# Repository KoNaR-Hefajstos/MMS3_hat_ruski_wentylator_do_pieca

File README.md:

# Hat ruski wentylator do pieca

## Sekcja 1: Dokumentacja Hat'a

### Krótki opis projektu
Dedykowany moduł sterujący przeznaczony do obsługi ruskiego wentylatora pieca . Urządzenie bazuje na mikrokontrolerze **CH32V003**, który realizuje zadania regulacji napięcia zasilania silnika, sterowania kluczem PWM, pomiaru prędkości obrotowej z czujnika Halla i reguluje prędkość obrotową przy użyciu regulatora PID.

Moduł wyposażono w przetwornicę podwyższającą (Boost) sterowaną cyfrowym potencjometrem MCP4161 oraz stopień wykonawczy typu **high-side switch** oparty na tranzystorze PMOS.

Komunikacja po I2C

### Zgodność ze standardem ChainBus

* ✅  Używa złącza ChainBus, nie zmienia jego miejsca ani pinoutu.
* ✅  Używa wyłącznie interfejsów I2C, SPI lub UART i nie inicjuje samodzielnie nowych transmisji (Nie jest master'em I2C albo SPI).
* ✅  Spełnia wymagania mechaniczne standardu (wymiary PCB, rozstaw otworów).
* ✅  Pobiera maksymalny prąd zgodny z ilością na jednego hat'a
* ❌ Obsługuje napięcie wejściowe BRD_VIN do wartości 48V. ---> napięcie wejściowe max 40V. Zawsze podaje napięcie wejściowe na wyjście wentylatora (J6 pin 3)

### Komunikacja i adresowanie

#### Adresacja I2C
Komunikacja z płytą główną ChainBus odbywa się za pośrednictwem magistrali I2C podłączonej do mikrokontrolera CH32V003.

| Układ (IC)   | Funkcja                              |     Adres I2C (7-bit)     |
| :----------- | :----------------------------------- | :-----------------------: |
| **CH32V003** | Mikrokontroler (zarządzanie modułem) | *Konfigurowalny w sofcie* |

### Pinout mikrokontrolera CH32V003

| Pin MCU | Nazwa sygnału | Kierunek | Opis funkcjonalny                                  |
| :------ | :------------ | :------: | :------------------------------------------------- |
| **PC0** | `PWM_GATE`    | Wyjście  | Sterowanie bramką PMOS (high-side switch)          |
| **PC1** | `SDA`         | Wej/Wyj  | Linia danych magistrali I2C (ChainBus)             |
| **PC2** | `SCL`         | Wejście  | Linia zegarowa magistrali I2C (ChainBus)           |
| **PC3** | `BOOST_EN`    | Wyjście  | Włączenie przetwornicy Boost (`1` = ON, `0` = OFF) |
| **PC4** | `V_MONITOR`   | Wejście  | Pomiar ADC napięcia silnika (dzielnik 36k / 2k)    |
| **PC5** | `SPI_SCK`     | Wyjście  | Zegar SPI do potencjometru MCP4161                 |
| **PC6** | `SPI_MOSI`    | Wyjście  | Dane wyjściowe SPI do potencjometru MCP4161        |
| **PC7** | `SPI_MISO`    | Wejście  | Dane wejściowe SPI z potencjometru MCP4161         |
| **PD0** | `HALL_INPUT`  | Wejście  | Sygnał z czujnika Halla wentylatora                |
| **PD2** | `SPI_CS_POT`  | Wyjście  | Wybór układu (Chip Select) dla MCP4161             |
| **PD3** | `GPIO_PD3`    | Wej/Wyj  | Wolny pin GPIO wyprowadzony na złącze J9           |
| **PD4** | `GPIO_PD4`    | Wej/Wyj  | Wolny pin GPIO wyprowadzony na złącze J9           |
| **PD5** | `USART_TX`    | Wyjście  | Port szeregowy TX (debugowanie, złącze J9)         |
| **PD6** | `USART_RX`    | Wejście  | Port szeregowy RX (złącze J9)                      |

---

### Pinout złączy zewnętrznych

#### J6 — Złącze wentylatora pieca
Złącze przeznaczone do bezpośredniego podłączenia ruskiego wentylatora.

| Pin złącza | Kolor przewodu z wentlatora | Nazwa sygnału | Opis                                                |
| :--------: | :-------------------------- | :------------ | :-------------------------------------------------- |
|   **1**    | Czarny                      | `GND`         | Wspólna masa układu                                 |
|   **2**    | Brązowy                     | `5V`          | Zasilanie układu Halla wentylatora                  |
|   **3**    | Niebieski                   | `VCC_MOTOR`   | Napięcie zasilające silnik wentylatora              |
|   **4**    | Biały/Żółty                 | `HALL`        | Wyjście czujnika Halla (sprzężenie zwrotne obrotów) |

#### J9 — Złącze wolnych pinów mcu

| Pin złącza | Sygnał | Opis                    |
| :--------: | :----- | :---------------------- |
|   **1**    | `GND`  | Masa układu             |
|   **2**    | `3V3`  | Zasilanie logiki 3.3V   |
|   **3**    | `PD3`  | Wolny port GPIO         |
|   **4**    | `PD4`  | Wolny port GPIO         |
|   **5**    | `PD5`  | GPIO + Wyjście USART TX |
|   **6**    | `PD6`  | GPIO + Wejście USART RX |

---

### Konfiguracja i zasada działania stopni wykonawczych

#### 1. Regulacja Napięcia (Przetwornica Boost)
Napięcie zasilania silnika jest generowane przez przetwornicę podwyższającą z poziomu wejściowego 12V. Napięcie wyjściowe regulowane jest przy użyciu potencjometru cyfrowego MCP4161 (5kΩ) działającego jako rezystor nastawny w feedback'u regulatora . Wyjście `P0B` podłączone jest z jednej strony, natomiast wyjścia `P0W` i `P0A` są ze sobą zwarte z drugiej.

Napięcie wyjściowe definiuje zależność:
$$U_{out} = 1.25 \times \left(1 + \frac{50\text{k}\Omega}{1.22\text{k}\Omega + R_{trim}}\right)$$

*   **⚠️ KRYTYCZNE OGRANICZENIE BEZPIECZEŃSTWA:** Mimo teoretycznego zakresu regulacji przetwornicy od 12V do 60V, **maksymalne dopuszczalne napięcie robocze wynosi 24V**. Przekroczenie tego progu spowoduje nieodwracalne uszkodzenie wentylatora, kondensatorów filtrujących oraz stopnia high-side switch. (24V silnika, a ~40V kondensatorów)
*   **Procedura bezpiecznego startu:** Przy każdym uruchomieniu mikrokontrolera, oprogramowanie musi natychmiast ustawić potencjometr MCP4161 na **maksymalną rezystancję (5kΩ)**, co wymusza minimalne napięcie startowe (ok. 11.3V). Dodatkowo, przetwornica Boost oraz klucz PWM muszą być domyślnie wyłączone (`BOOST_EN` = `0`, `PWM_GATE` = `0`).
*   **Charakterystyka Boost:** Nawet w stanie wyłączonym (`BOOST_EN` = `0`), napięcie wejściowe 12V będzie stale obecne na wyjściu przetwornicy.

#### 2. Bonusowy Stopień wykonawczy (High-Side Switch PMOS)
Sterowanie dopływem prądu z przetwornicy do silnika wentylatora odbywa się za pomocą klucza high-side switch opartego na tranzystorze PMOS.

*   **Konfiguracja domyślna (Bypass):** Na płycie fabrycznie wlutowany jest rezystor **R6**, który zwiera (pomija) tranzystor PMOS. W tym trybie silnik zasilany jest stale bezpośrednio z wyjścia przetwornicy Boost, a regulacja obrotów odbywa się wyłącznie poprzez zmianę jej napięcia wyjściowego.
*   **Konfiguracja zaawansowana (Sterowanie PWM):** W celu sterowania silnikiem za pomocą cięcia prądu sygnałem PWM z pinu `PC0` mikrokontrolera, należy **odlutować rezystor R6**.
*   **Element wykonawczy:** Na płycie domyślnie znajduje się tranzystor PMOS **AO3401A** (obudowa SOT-23, parametry: 30V, 4A), który jest w pełni wystarczający do obsługi docelowego wentylatora piecowego. Na laminacie pozostawiono jednak alternatywne, wolne miejsce na montaż mocniejszego tranzystora w obudowie **TO-220** na wypadek nietypowych modyfikacji.

#### A po ludzku
* Masz wentlator, sterujesz jego prękością dając mu różne napięcie i/lub PWM
* Napięciem sterujesz przez potencjometr cyfrowy
* PWM przez high side switch (który jest domyślnie z'bypass'owany czyli trzeba wylutować rezystor żeby go użyć)
* Przetworke możesz właczyć/wyłączyć, ale zawsze daje VIN na wyjście silnika
* Prędkość obrotową wentylatora możesz odczytać przez częstotliwosć impulsów na czujnika halla
* A napięcie wyjściowe przetworki jest po dzielniku napięć na pin'ie PC4 (dzielnik dzieli VCC silnika przez 18)

---

### Gotowe arkusze hierarchiczne
W projekcie zaprojektowano i użyto następujących arkuszy hierarchicznych:
* **CH32v003** – Schemat mikrokontrolera głównego wraz z elementami pasywnymi i złączem programowania
* **Boost converter** – Układ regulowanej przetwornicy podwyższającej napięcie z 12V na zakres do ~60V sterowanej cyfrowym potencjometrem MCP4161.
* **High side switch** – Blok High-side switch'a na PMOS (AO3401A) sterowanego sygnałem PWM z układem typu totem pole do drive'owania bramki
---

## Sekcja 2: Specyfikacja standardu ChainBus

### Architektura i łączenie modułów
Standard ChainBus umożliwia modułowe łączenie hatów. Na jednym MMS3 można zamontować pionowo **do 8 hat'ów**. Połączenie realizowane jest poprzez wpięcie złącza męskiego kolejnego hat'a w złącze żeńskie poprzedniego

### Komunikacja i sterowanie
Magistrala ChainBus jest w pełni cyfrowa. Płyta główna nie steruje bezpośrednio sygnałami ogólnego przeznaczenia (GPIO) na poszczególnych hat'ach. Wszelkie operacje (np. obsługa diod LED, odczyt krańcówek, generowanie sygnałów PWM) muszą być realizowane przez dedykowane układy scalone (np. ekspandery portów, sterowniki) komunikujące się przez interfejsy systemowe.

*Przykład:*
`MCU` $\rightarrow$ `Expander GPIO po I2C` $\rightarrow$ `Dioda LED`

Wybór aktywnego modułu realizowany jest przez układ przełącznika magistrali (bus switch) na płycie głównej. Dzięki temu linie I2C, SPI i UART są niezależne dla każdego hat'a (brak konfliktów adresów I2C między różnymi hatami).
* **Identyfikacja:** Każdy moduł powinien posiadać pamięć EEPROM na magistrali I2C w celu identyfikacji płyty przez system - układ M24C64-W skonfigurowany na adres `1010000` przy liniach adresowych A0, A1, A2 zwartych do masy.

### Zasilanie
Złącze ChainBus dostarcza następujące linie zasilania:

| Magistrala zasilania | Napięcie znamionowe | Maksymalny prąd (łączny dla 8 hatów) | Szacowany prąd na jeden hat |
| :------------------- | :-----------------: | :----------------------------------: | :-------------------------: |
| **5V**               |        5.0 V        |                1.0 A                 |           125 mA            |
| **12V stby**         |       12.0 V        |                0.5 A                 |            65 mA            |
| **BRD_VIN**          |   12.0 V – 48.0 V   |                1.5 A                 |           185 mA            |

*   Komponenty podłączone do linii `BRD_VIN` muszą być przystosowane do pracy z napięciem od 12V do **48 V**.
*   W przypadku zapotrzebowania na wyższą moc, dopuszczalne jest zastosowanie dodatkowego złącza zasilania XT60 (obciążalność do ok. 60 A).

### Wymagania mechaniczne i złącza
* **Wymiary PCB:** Niedozwolona jest zmiana obrysu płytki oraz położenia otworów montażowych, aby zachować kompatybilność mechaniczną.
* **Pozycjonowanie złączy ChainBus:** Położenie złącza standardu 2x16 SMD (raster 2.54 mm) musi być zgodne z szablonem. Złącze żeńskie montowane jest na stronie FRONT, natomiast złącze męskie na stronie BACK.
* **Interfejsy zewnętrzne:** Złącza wejścia/wyjścia (domyślnie standard JST-XH 2.5 mm o obciążalności do 3 A) oraz opcjonalne złącze XT60 powinny być umieszczone przy dolnej krawędzi płytki. Elementy regulacyjne i sygnalizacyjne (potencjometry, przełączniki, diody LED) należy lokalizować przy prawej krawędzi płytki.
* **Komponenty** Wszystkie komponenty powinny być na stronie front płytki żeby nie haczyły o elementy ze wcześniejszego hat'a

---

## Sekcja 3: Licencje

### Licencje projektu

*   **PCB:** CERN-OHL-P
*   **Software:** MIT License

[Template](https://github.com/KoNaR-Hefajstos/MMS3_hat_templates/) jest na licencji CC0 1.0 Universal. **Reszta projektu nie jest na tej licencji**

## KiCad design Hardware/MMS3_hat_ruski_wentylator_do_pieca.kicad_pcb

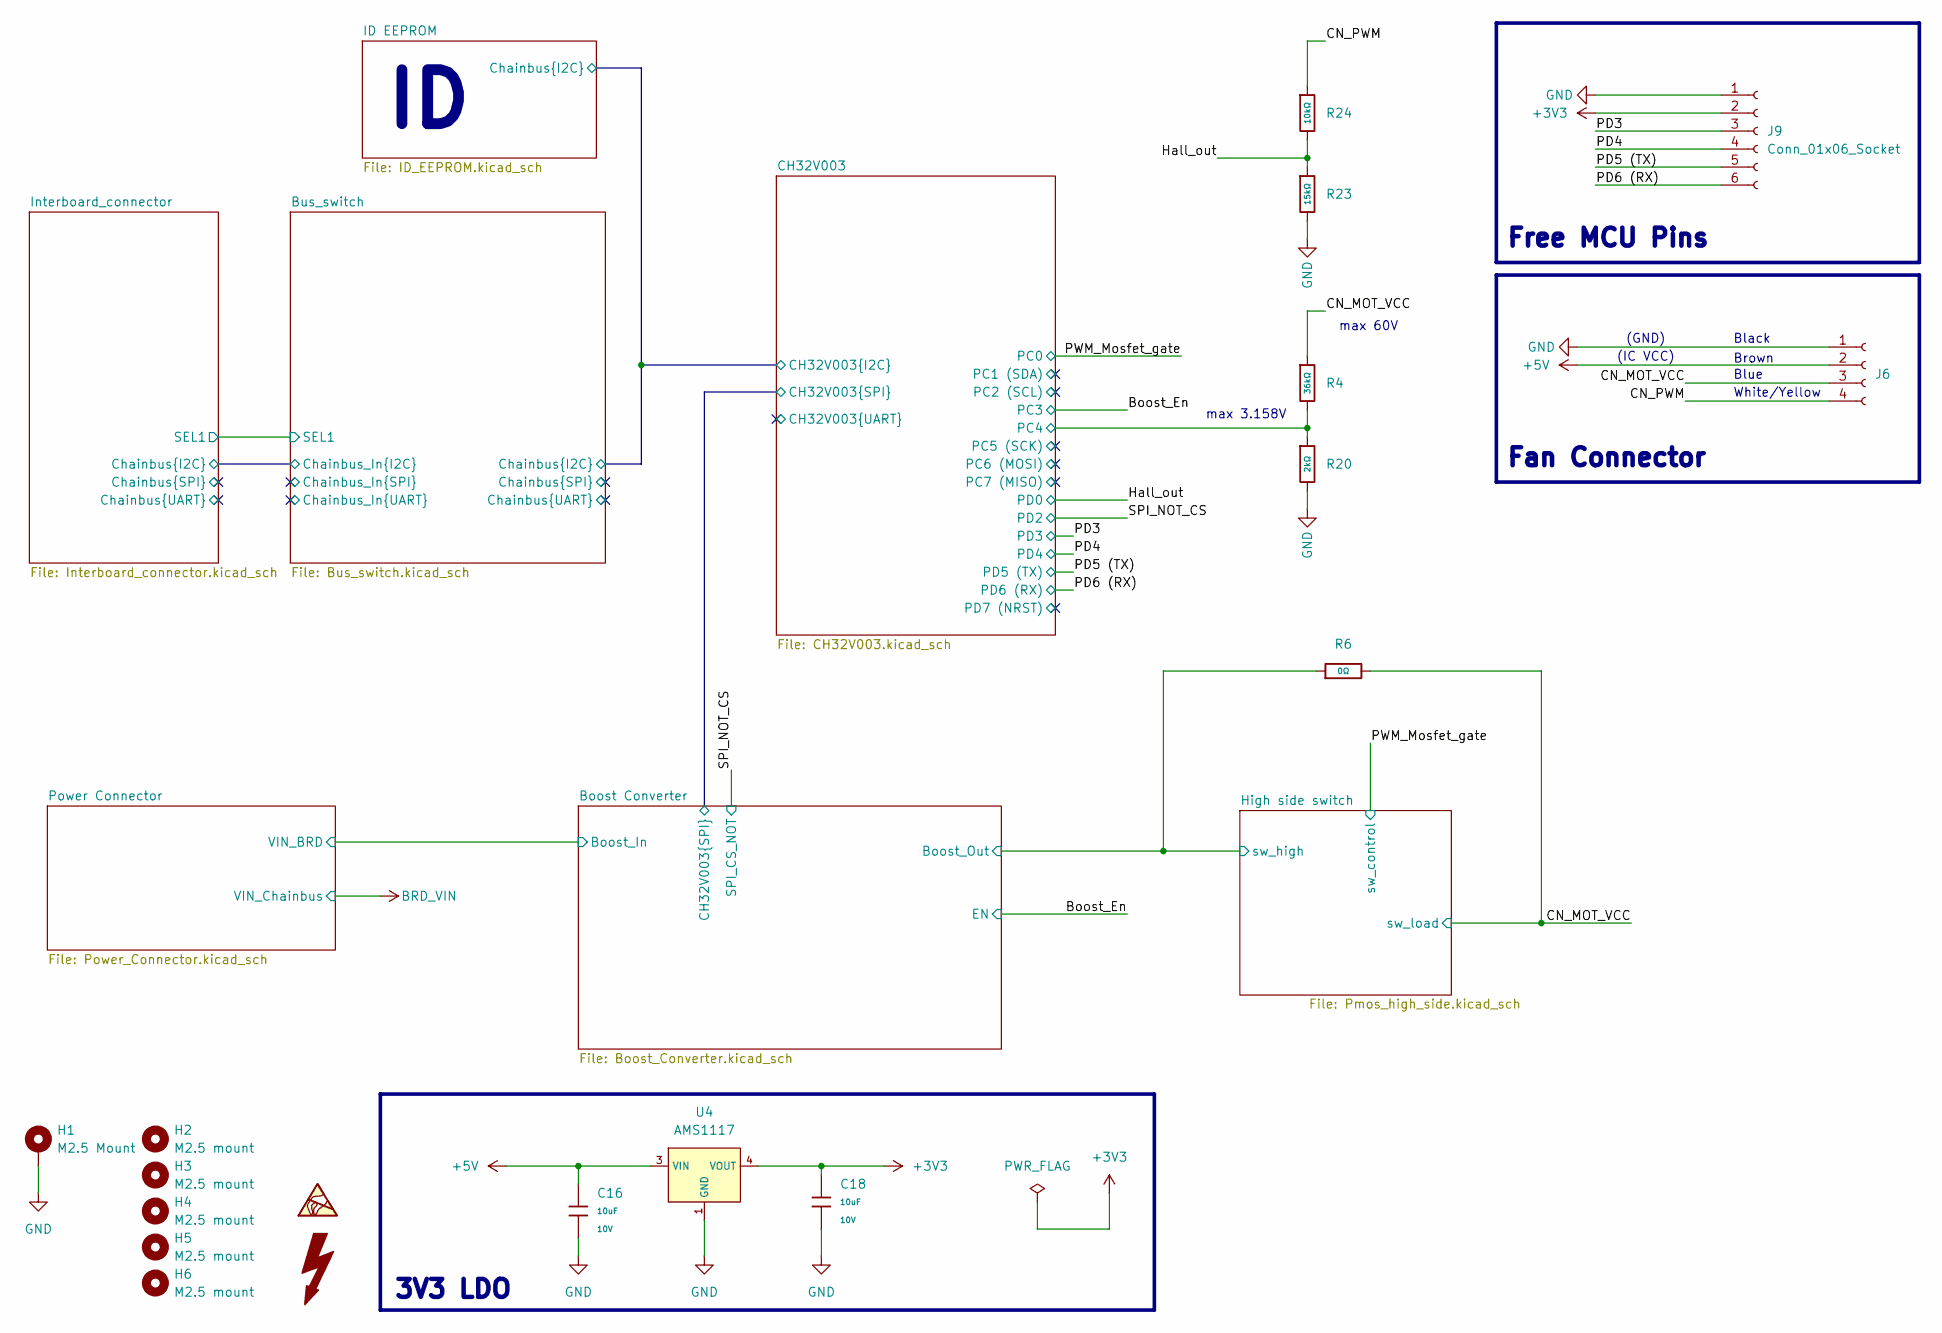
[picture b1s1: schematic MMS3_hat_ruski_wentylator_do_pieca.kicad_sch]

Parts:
C16, C18: 10uF; C_0603; Voltage Rated 10V; Tolerance ±10%; Part CL10A106KP8NNNC; LCSC C19702
H1: M2.5 Mount; MountingHole_2.7mm_M2.5_DIN965_Pad_TopOnly
H2, H3, H4, H5, H6: M2.5 mount; MountingHole_2.7mm_M2.5
J6: Conn_01x04_Socket; JST_XH_S4B-XH-A_1x04_P2.50mm_Horizontal
J9: Conn_01x06_Socket; JST_XH_S6B-XH-A_1x06_P2.50mm_Horizontal
R4: 36kΩ; R_0603; Overload Voltage (Max) 75V; Tolerance ±1%; Part 0603WAF3602T5E; LCSC C23147
R6: 0Ω; R_0603; Overload Voltage (Max) 75V; Tolerance ±1%; Part 0603WAF0000T5E; LCSC C21189
R20: 2kΩ; R_0603; Overload Voltage (Max) 75V; Tolerance ±1%; Part 0603WAF2001T5E; LCSC C22975
R23: 15kΩ; R_0402; Overload Voltage (Max) 50V; Tolerance ±1%; Part 0402WGF1502TCE; LCSC C25756
R24: 10kΩ; R_0402; Overload Voltage (Max) 50V; Tolerance ±1%; Part 0402WGF1002TCE; LCSC C25744
U4: AMS1117; SOT-223-3_L6.5-W3.4-P2.30-LS7.0-BR; Output Voltage 3.3V; Dropout Voltage 1.3V@(800mA); Part AMS1117-3.3; LCSC C6186

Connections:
+3V3: C18.1, J9.2, U4.2 (VOUT), U4.4 (VOUT); also elsewhere on the board
+5V: C16.1, J6.2, U4.3 (VIN); also elsewhere on the board
/Boost Converter/Boost_Out: R6.1; also elsewhere on the board
/CH32V003/PC4: R4.2, R20.1; also elsewhere on the board
/CN_MOT_VCC: J6.3, R4.1, R6.2; also elsewhere on the board
/CN_PWM: J6.4, R24.1
/Hall_out: R23.1, R24.2; also elsewhere on the board
/PD3: J9.3; also elsewhere on the board
/PD4: J9.4; also elsewhere on the board
/PD5 (TX): J9.5; also elsewhere on the board
/PD6 (RX): J9.6; also elsewhere on the board
GND: C16.2, C18.2, H1.1 (1_1), J6.1, J9.1, R20.2, R23.2, U4.1 (GND); also elsewhere on the board

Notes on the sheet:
(IC VCC)
Blue
max 60V
Fan Connector
White/Yellow
(GND)
3V3 LDO
Free MCU Pins
max 3.158V
Brown
Black

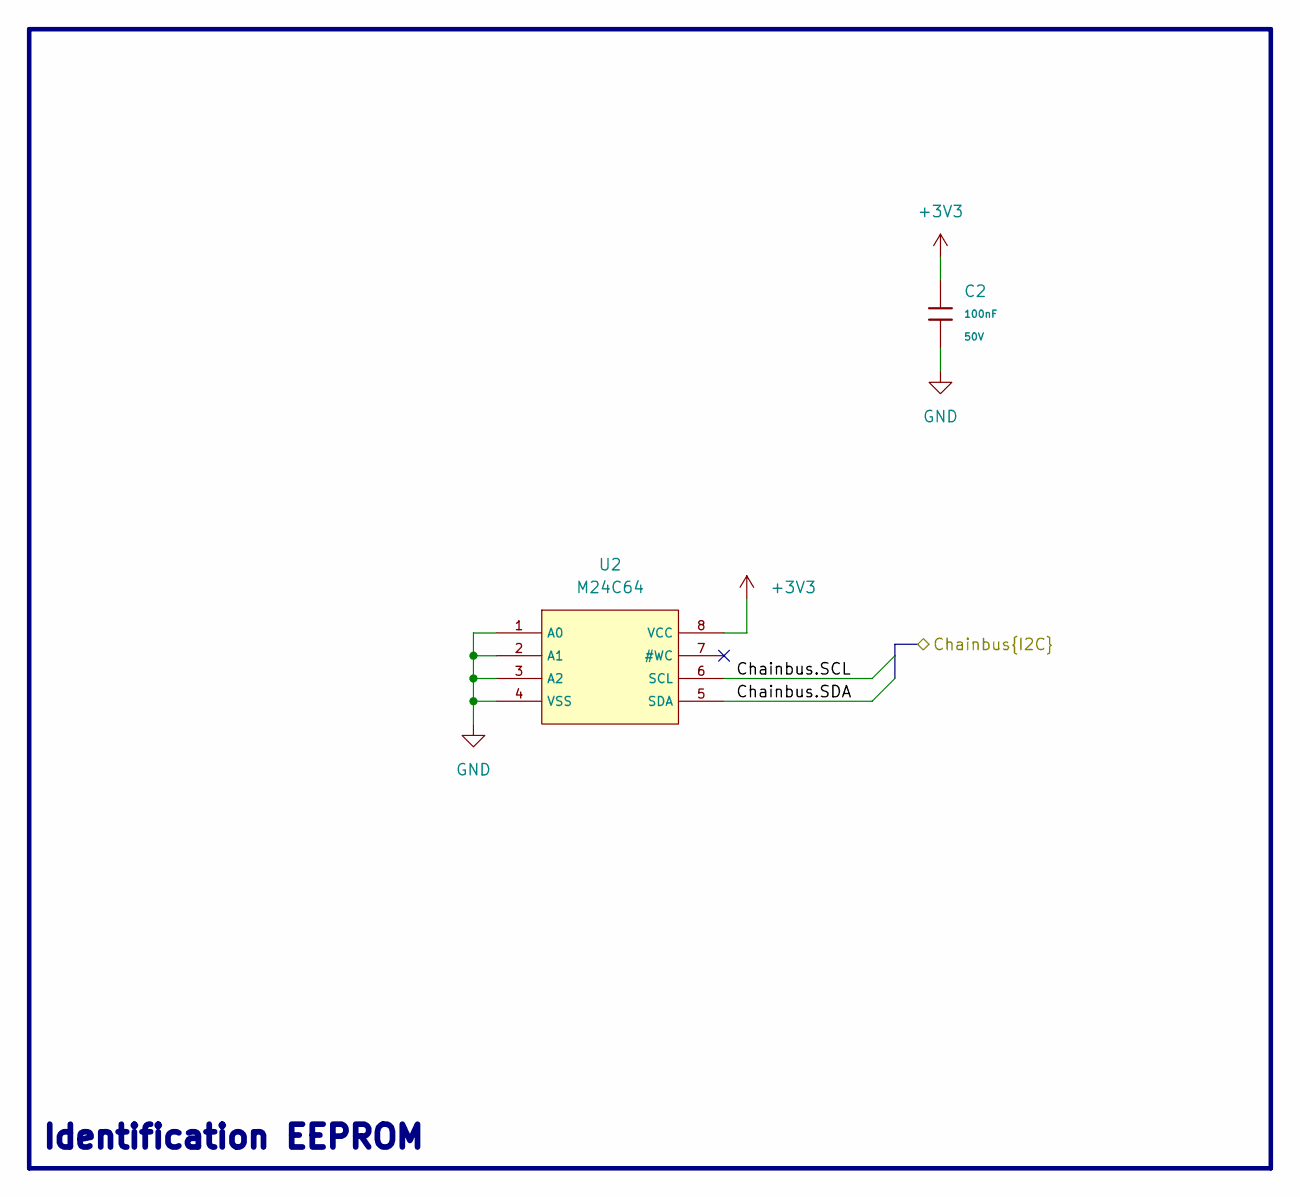
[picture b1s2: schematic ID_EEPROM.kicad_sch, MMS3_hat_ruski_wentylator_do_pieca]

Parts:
C2: 100nF; C_0603; Voltage Rated 50V; Tolerance ±10%; Part CC0603KRX7R9BB104; LCSC C14663
U2: M24C64; SOIC-8_L5.0-W4.0-P1.27-LS6.0-BL; Supply Voltage 1.8V~5.5V; Part M24C64-RMN6TP; LCSC C79988

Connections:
+3V3: C2.1, U2.8 (VCC); also elsewhere on the board
/Bus_switch/Chainbus.SCL: U2.6 (SCL); also elsewhere on the board
/Bus_switch/Chainbus.SDA: U2.5 (SDA); also elsewhere on the board
GND: C2.2, U2.1 (A0), U2.2 (A1), U2.3 (A2), U2.4 (VSS); also elsewhere on the board

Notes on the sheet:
Identification EEPROM

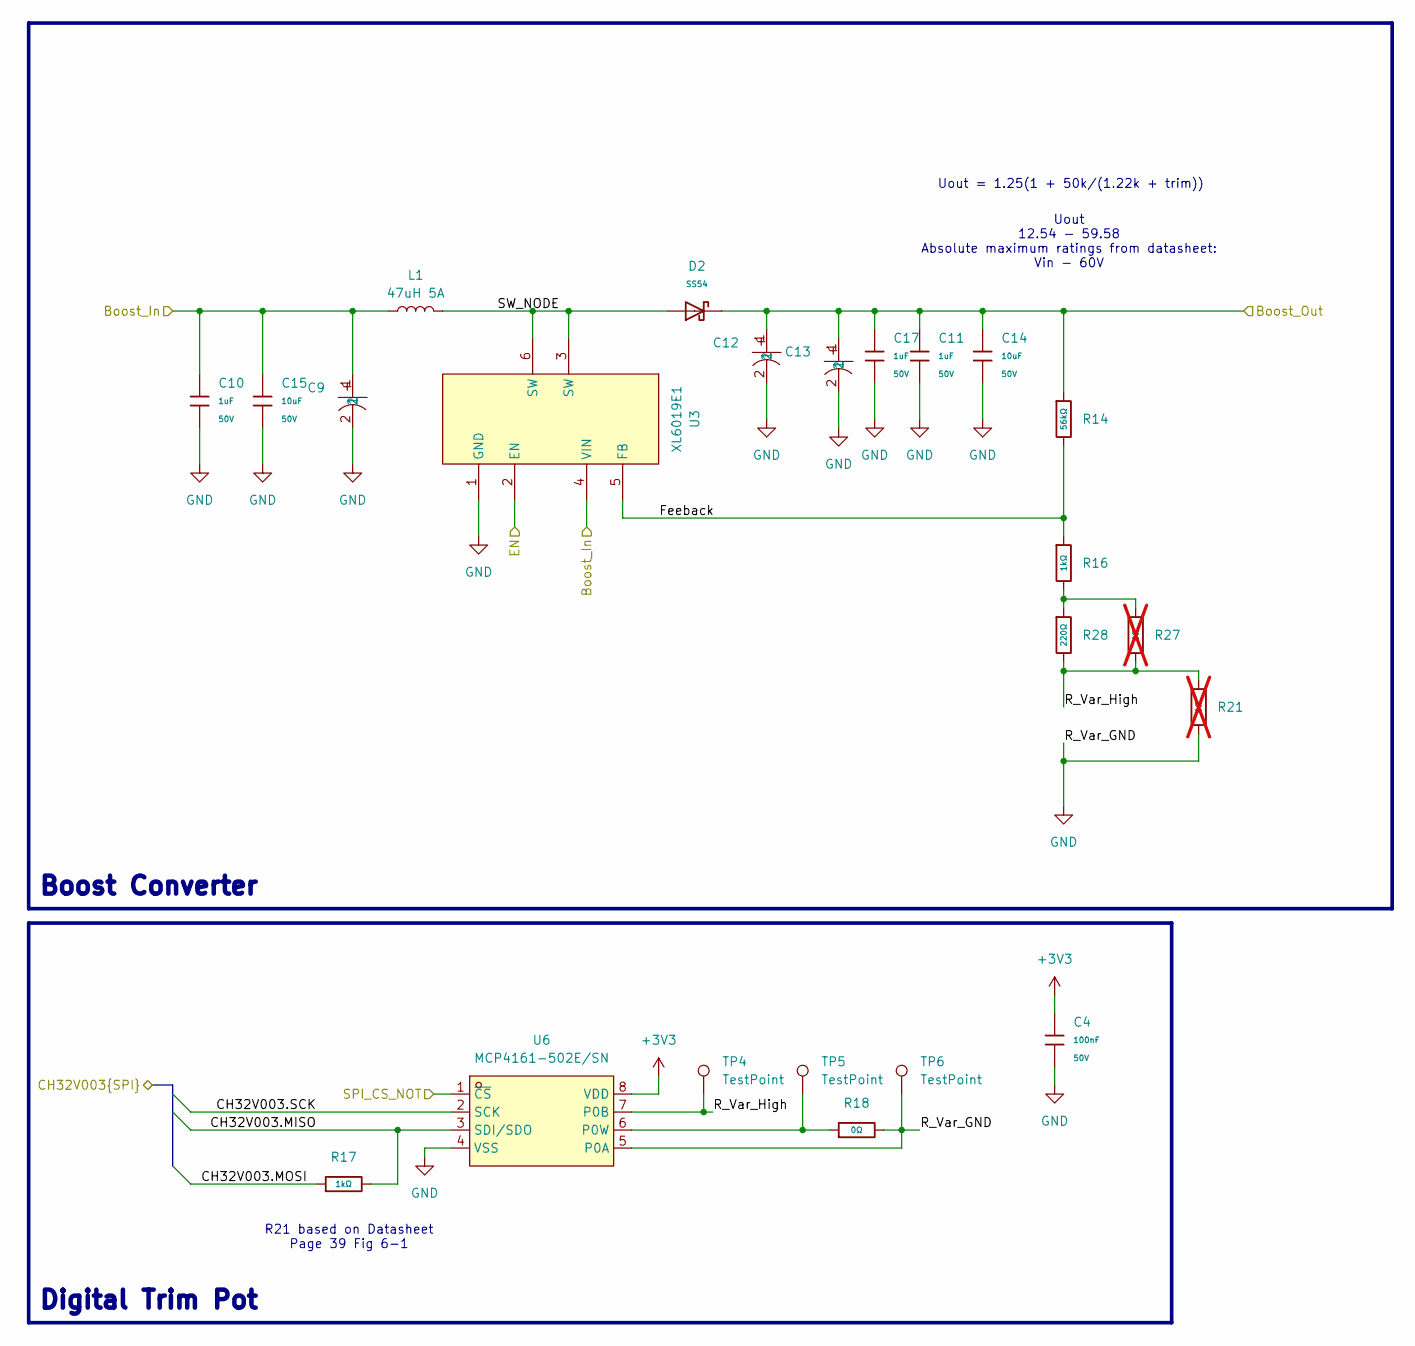
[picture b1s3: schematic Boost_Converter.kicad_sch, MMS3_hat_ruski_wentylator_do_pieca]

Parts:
C4: 100nF; C_0603; Voltage Rated 50V; Tolerance ±10%; Part CC0603KRX7R9BB104; LCSC C14663
C9, C12, C13: Whatever the chinese man has (preferably 220uF); CP_Elec_10x10; MPN EEVFK1J221Q; LCSC Part C178727
C10, C11, C17: 1uF; C_0603; Voltage Rated 50V; Tolerance ±10%; Part CL10A105KB8NNNC; LCSC C15849
C14, C15: 10uF; C_1206; Voltage Rated 50V; Tolerance ±10%; Part CL31A106KBHNNNE; LCSC C13585
D2: SS54; D_SMA; Forward Voltage (Vf@If) 550mV@5A; Reverse Voltage (Vr) 40V; Part SS54; LCSC C22452
L1: 47uH 5A; L_12x12mm_H6mm
R14: 56kΩ; R_0603; Overload Voltage (Max) 75V; Tolerance ±1%; Part 0603WAF5602T5E; LCSC C23206
R16, R17: 1kΩ; R_0603; Overload Voltage (Max) 75V; Tolerance ±1%; Part 0603WAF1001T5E; LCSC C21190
R18: 0Ω; R_0603; Overload Voltage (Max) 75V; Tolerance ±1%; Part 0603WAF0000T5E; LCSC C21189
R21, R27: 0Ω; R_0603; Overload Voltage (Max) 75V; Tolerance ±1%; Part 0603WAF0000T5E; LCSC C21189; not fitted
R28: 220Ω; R_0603; Overload Voltage (Max) 75V; Tolerance ±1%; Part 0603WAF2200T5E; LCSC C22962
TP4, TP5, TP6: TestPoint; TestPoint_Pad_D1.5mm
U3: XL6019E1; TO-263-5_L10.2-W9.9-P1.70-LS14.4-TL; MPN XL6019E1; LCSC Part C73018
U6: MCP4161-502E/SN; SOIC-8_L4.9-W3.9-P1.27-LS6.0-BL; MPN MCP4161-502E/SN; LCSC Part C636080

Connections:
+3V3: C4.1, U6.8 (VDD); also elsewhere on the board
/Boost Converter/Boost_In: C9.1, C10.1, C15.1, L1.1, U3.4 (VIN); also elsewhere on the board
/Boost Converter/Boost_Out: C11.1, C12.1, C13.1, C14.1, C17.1, D2.1, R14.1; also elsewhere on the board
/Boost Converter/CH32V003.MISO: R17.2, U6.3 (SDI/SDO); also elsewhere on the board
/Boost Converter/CH32V003.MOSI: R17.1; also elsewhere on the board
/Boost Converter/CH32V003.SCK: U6.2 (SCK); also elsewhere on the board
/Boost Converter/Feeback: R14.2, R16.1, U3.5 (FB)
/Boost Converter/R_Var_High: R21.2, R27.1, R28.2, TP4.1 (1_1), U6.7 (P0B)
/Boost Converter/SW_NODE: D2.2, L1.2, U3.3 (SW), U3.6 (SW)
/Boost_En: U3.2 (EN); also elsewhere on the board
/SPI_NOT_CS: U6.1 (~CS); also elsewhere on the board
GND: C4.2, C9.2, C10.2, C11.2, C12.2, C13.2, C14.2, C15.2, C17.2, R18.2, R21.1, TP6.1 (1_1), U3.1 (GND), U6.4 (VSS), U6.5 (P0A); also elsewhere on the board
unnamed: R16.2, R27.2, R28.1
unnamed: R18.1, TP5.1 (1_1), U6.6 (P0W)

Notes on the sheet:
Uout = 1.25(1 + 50k/(1.22k + trim))
Boost Converter
Uout 12.54 - 59.58 Absolute maximum ratings from datasheet: Vin - 60V
R21 based on Datasheet Page 39 Fig 6-1
Digital Trim Pot

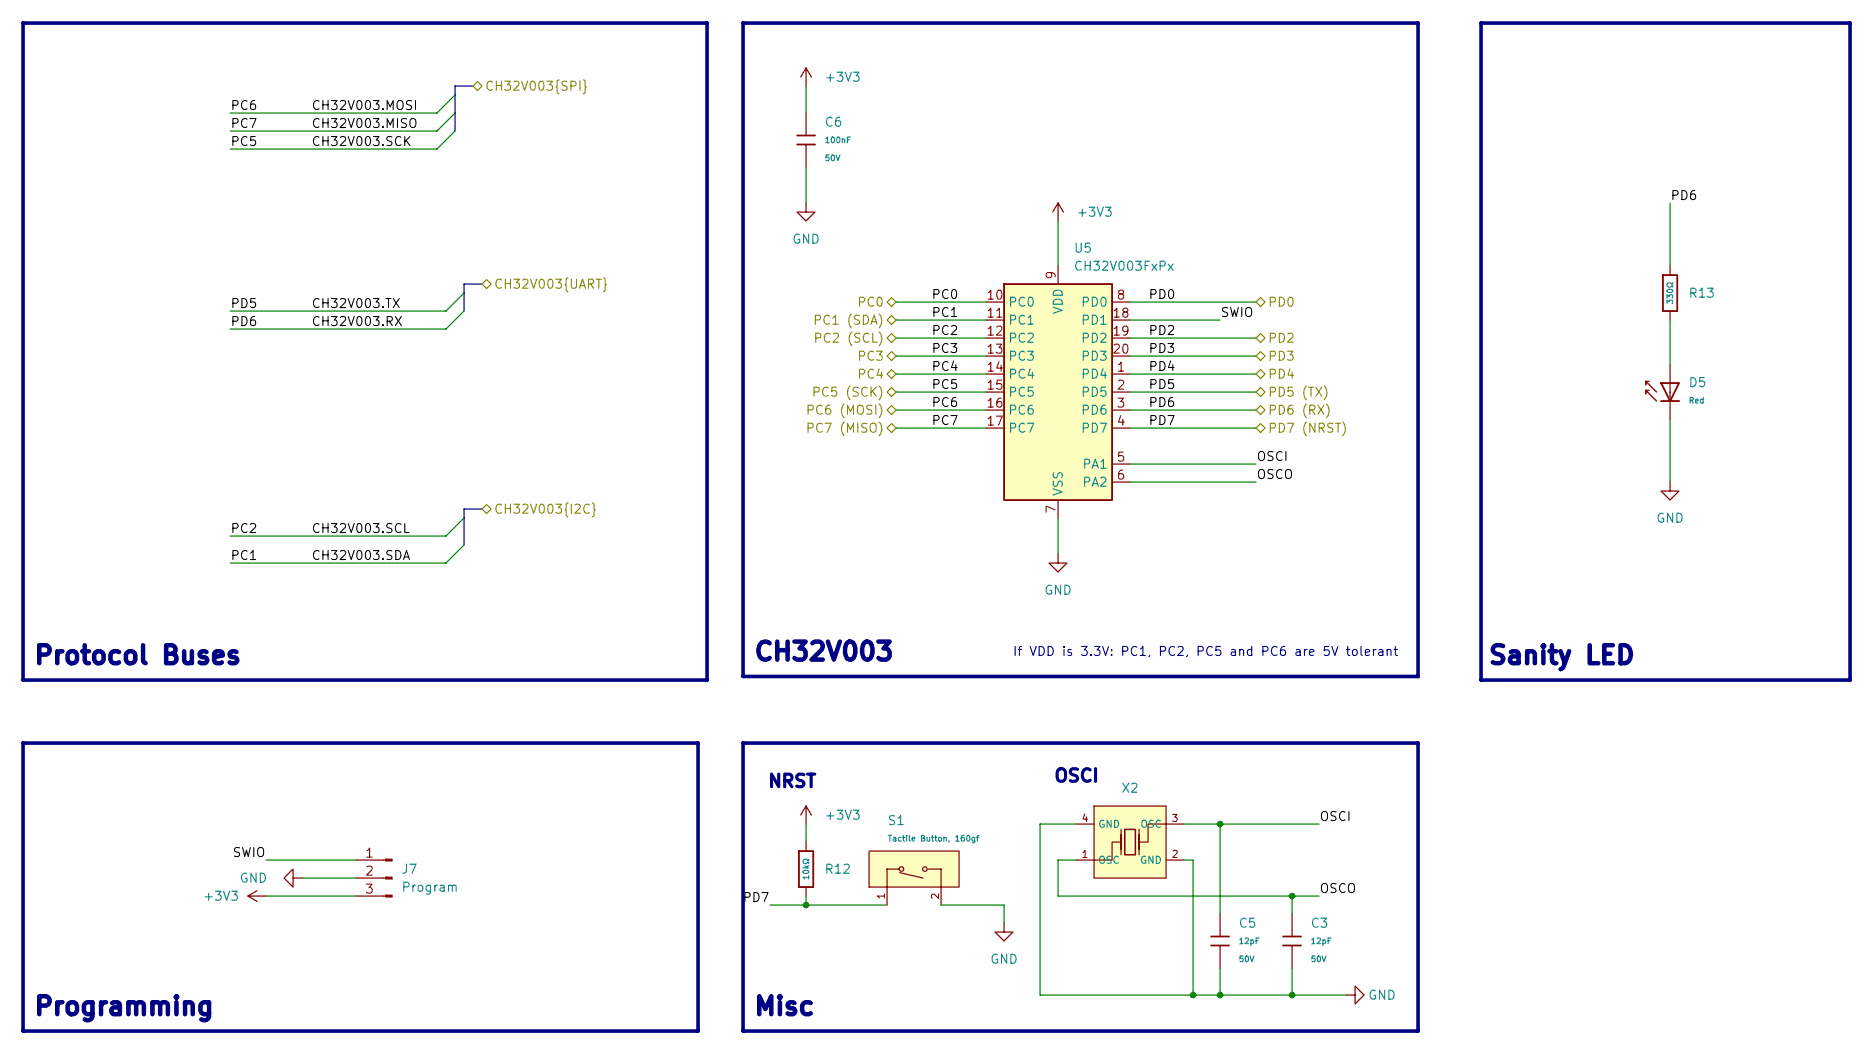
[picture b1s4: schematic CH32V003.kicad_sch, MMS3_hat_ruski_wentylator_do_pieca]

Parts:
C3, C5: 12pF; C_0603; Voltage Rated 50V; Tolerance ±5%; Part CL10C120JB8NNNC; LCSC C38523
C6: 100nF; C_0603; Voltage Rated 50V; Tolerance ±10%; Part CC0603KRX7R9BB104; LCSC C14663
D5: Red; D_0603; Part KT-0603R; LCSC C2286
J7: Program; JST_XH_B3B-XH-A_1x03_P2.50mm_Vertical
R12: 10kΩ; R_0402; Overload Voltage (Max) 50V; Tolerance ±1%; Part 0402WGF1002TCE; LCSC C25744
R13: 330Ω; R_0402; Overload Voltage (Max) 50V; Tolerance ±1%; Part 0402WGF3300TCE; LCSC C25104
S1: Tactile Button, 160gf; SW_TS-1088-AR02016; Voltage Rating (Dc) 12V; Part TS-1088-AR02016; LCSC C720477
U5: CH32V003FxPx; TSSOP-20_4.4x6.5mm_P0.65mm
X2: X322525MOB4SI; OSC-SMD_4P-L3.2-W2.5-BL; Frequency Tolerance ±10ppm; Part X322525MOB4SI; LCSC C9006

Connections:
+3V3: C6.1, J7.3, R12.1, U5.9 (VDD); also elsewhere on the board
/Boost Converter/CH32V003.MISO: U5.17 (PC7); also elsewhere on the board
/Boost Converter/CH32V003.MOSI: U5.16 (PC6); also elsewhere on the board
/Boost Converter/CH32V003.SCK: U5.15 (PC5); also elsewhere on the board
/Boost_En: U5.13 (PC3); also elsewhere on the board
/Bus_switch/Chainbus.SCL: U5.12 (PC2); also elsewhere on the board
/Bus_switch/Chainbus.SDA: U5.11 (PC1); also elsewhere on the board
/CH32V003/OSCI: C5.1, U5.5 (PA1), X2.3 (OSC)
/CH32V003/OSCO: C3.1, U5.6 (PA2), X2.1 (OSC)
/CH32V003/PC4: U5.14 (PC4); also elsewhere on the board
/CH32V003/PD7: R12.2, S1.1 (A), U5.4 (PD7)
/CH32V003/SWIO: J7.1, U5.18 (PD1)
/Hall_out: U5.8 (PD0); also elsewhere on the board
/PD3: U5.20 (PD3); also elsewhere on the board
/PD4: U5.1 (PD4); also elsewhere on the board
/PD5 (TX): U5.2 (PD5); also elsewhere on the board
/PD6 (RX): R13.1, U5.3 (PD6); also elsewhere on the board
/PWM_Mosfet_gate: U5.10 (PC0); also elsewhere on the board
/SPI_NOT_CS: U5.19 (PD2); also elsewhere on the board
GND: C3.2, C5.2, C6.2, D5.1, J7.2, S1.2 (B), U5.7 (VSS), X2.2 (GND), X2.4 (GND); also elsewhere on the board
unnamed: D5.2, R13.2

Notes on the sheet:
NRST
Sanity LED
If VDD is 3.3V: PC1, PC2, PC5 and PC6 are 5V tolerant
CH32V003
OSCI
Protocol Buses
Misc
Programming

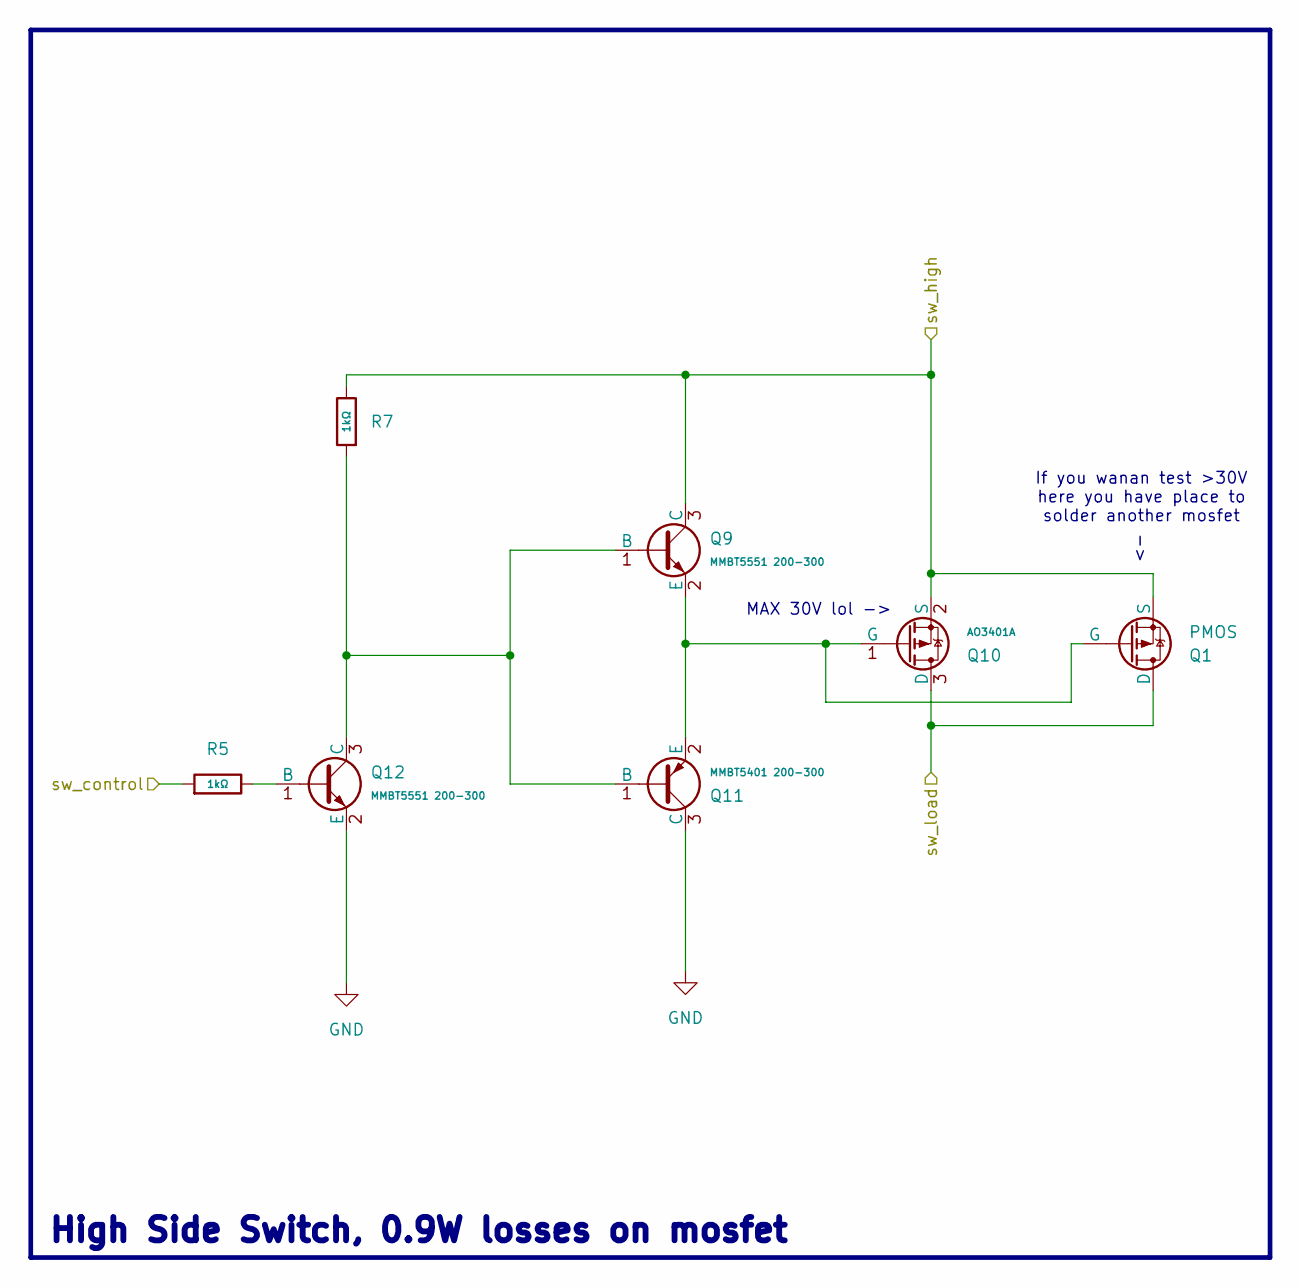
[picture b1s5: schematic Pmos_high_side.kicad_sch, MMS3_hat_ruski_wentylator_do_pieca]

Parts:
Q1: PMOS; TO-220-3_Vertical
Q9, Q12: MMBT5551 200-300; Q_SOT-23; Part MMBT5551(RANGE:200-300); LCSC C2145
Q10: AO3401A; Q_SOT-23; Part AO3401A; LCSC C15127
Q11: MMBT5401 200-300; Q_SOT-23; Part MMBT5401(RANGE:200-300); LCSC C8326
R5, R7: 1kΩ; R_0603; Overload Voltage (Max) 75V; Tolerance ±1%; Part 0603WAF1001T5E; LCSC C21190

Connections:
/Boost Converter/Boost_Out: Q1.3 (S), Q9.3 (C), Q10.2 (S), R7.2; also elsewhere on the board
/CN_MOT_VCC: Q1.1 (D), Q10.3 (D); also elsewhere on the board
/PWM_Mosfet_gate: R5.1; also elsewhere on the board
GND: Q11.3 (C), Q12.2 (E); also elsewhere on the board
unnamed: Q1.2 (G), Q9.2 (E), Q10.1 (G), Q11.2 (E)
unnamed: Q9.1 (B), Q11.1 (B), Q12.3 (C), R7.1
unnamed: Q12.1 (B), R5.2

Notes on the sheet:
If you wanan test >30V here you have place to solder another mosfet
MAX 30V lol ->
High Side Switch, 0.9W losses on mosfet

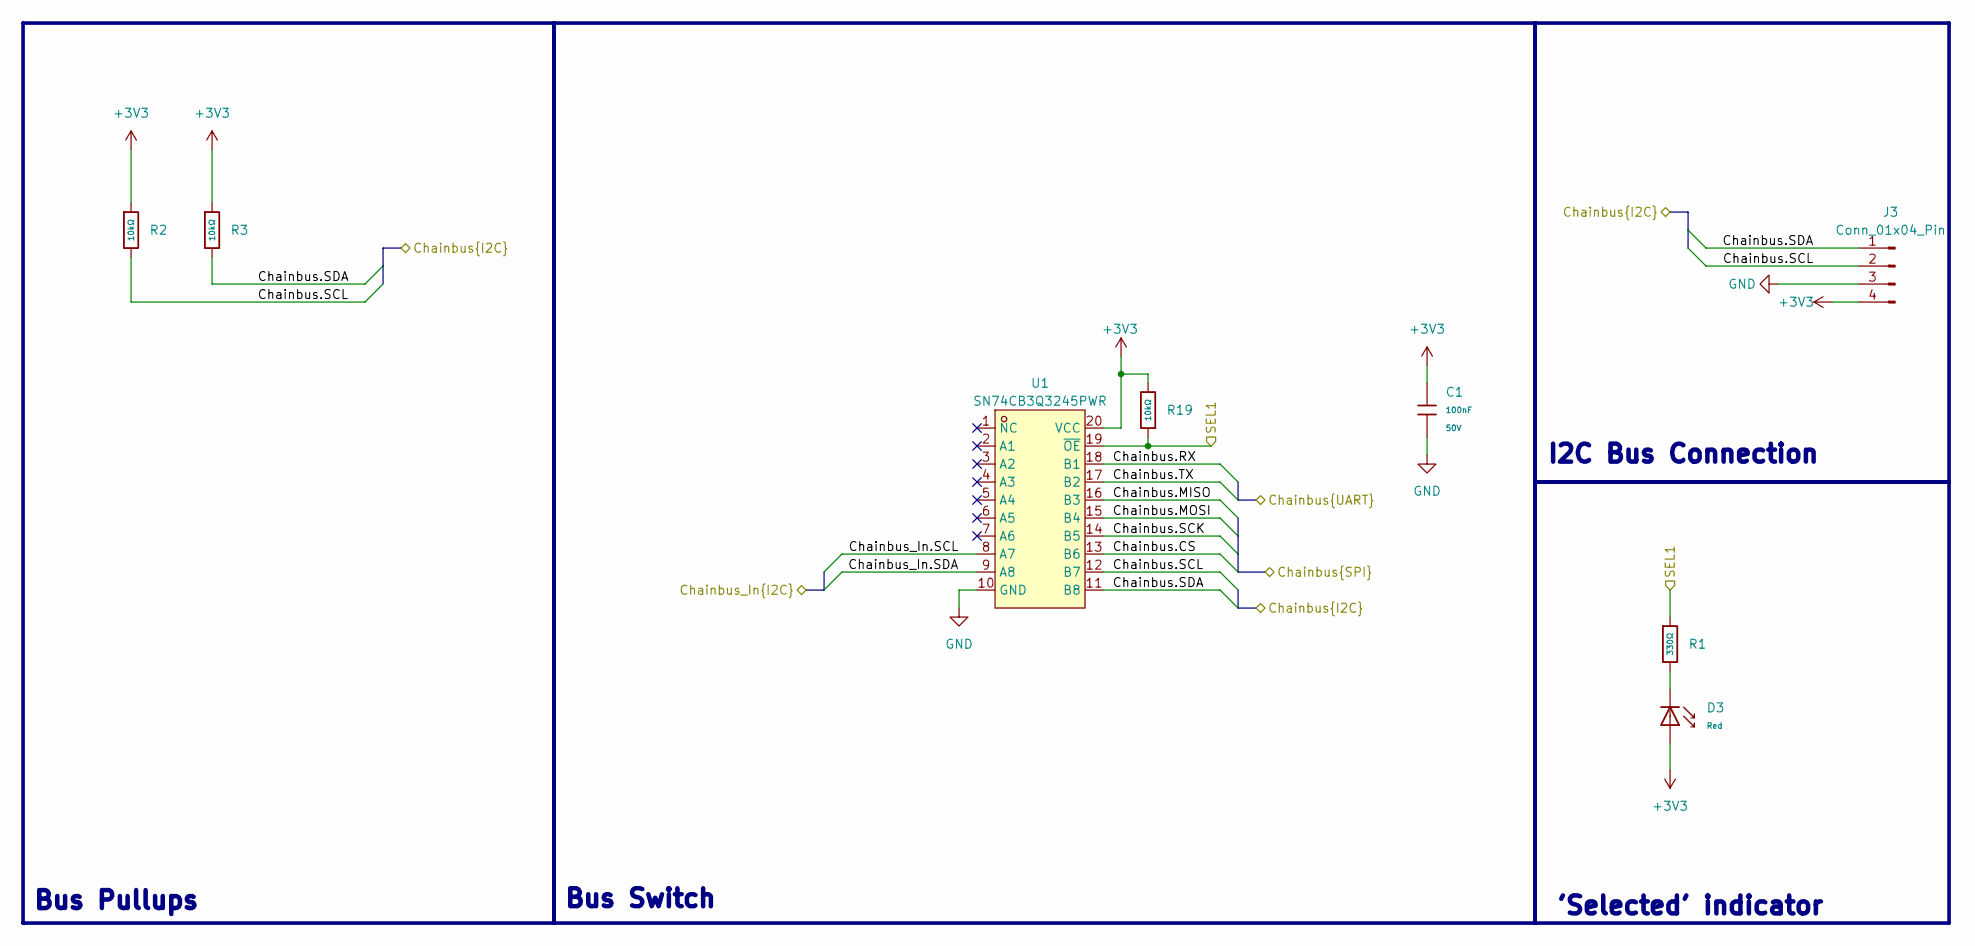
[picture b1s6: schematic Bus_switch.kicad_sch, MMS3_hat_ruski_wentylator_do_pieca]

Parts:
C1: 100nF; C_0603; Voltage Rated 50V; Tolerance ±10%; Part CC0603KRX7R9BB104; LCSC C14663
D3: Red; D_0603; Part KT-0603R; LCSC C2286
J3: Conn_01x04_Pin; PinHeader_1x04_P2.54mm_Vertical
R1: 330Ω; R_0402; Overload Voltage (Max) 50V; Tolerance ±1%; Part 0402WGF3300TCE; LCSC C25104
R2, R3: 10kΩ; R_0603; Overload Voltage (Max) 75V; Tolerance ±1%; Part 0603WAF1002T5E; LCSC C25804
R19: 10kΩ; R_0402; Overload Voltage (Max) 50V; Tolerance ±1%; Part 0402WGF1002TCE; LCSC C25744
U1: SN74CB3Q3245PWR; TSSOP-20_L6.5-W4.4-P0.65-LS6.4-BL; MPN SN74CB3Q3245PWR; LCSC Part C470961

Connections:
+3V3: C1.1, D3.2, J3.4, R2.1, R3.1, R19.2, U1.20 (VCC); also elsewhere on the board
/Bus_switch/Chainbus.CS: U1.13 (B6)
/Bus_switch/Chainbus.MISO: U1.16 (B3)
/Bus_switch/Chainbus.MOSI: U1.15 (B4)
/Bus_switch/Chainbus.RX: U1.18 (B1)
/Bus_switch/Chainbus.SCK: U1.14 (B5)
/Bus_switch/Chainbus.SCL: J3.2, R2.2, U1.12 (B7); also elsewhere on the board
/Bus_switch/Chainbus.SDA: J3.1, R3.2, U1.11 (B8); also elsewhere on the board
/Bus_switch/Chainbus.TX: U1.17 (B2)
/Bus_switch/Chainbus_In.SCL: U1.8 (A7); also elsewhere on the board
/Bus_switch/Chainbus_In.SDA: U1.9 (A8); also elsewhere on the board
/Bus_switch/SEL1: R1.1, R19.1, U1.19 (~OE); also elsewhere on the board
GND: C1.2, J3.3, U1.10 (GND); also elsewhere on the board
unnamed: D3.1, R1.2

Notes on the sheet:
Bus Switch
'Selected' indicator
Bus Pullups
I2C Bus Connection

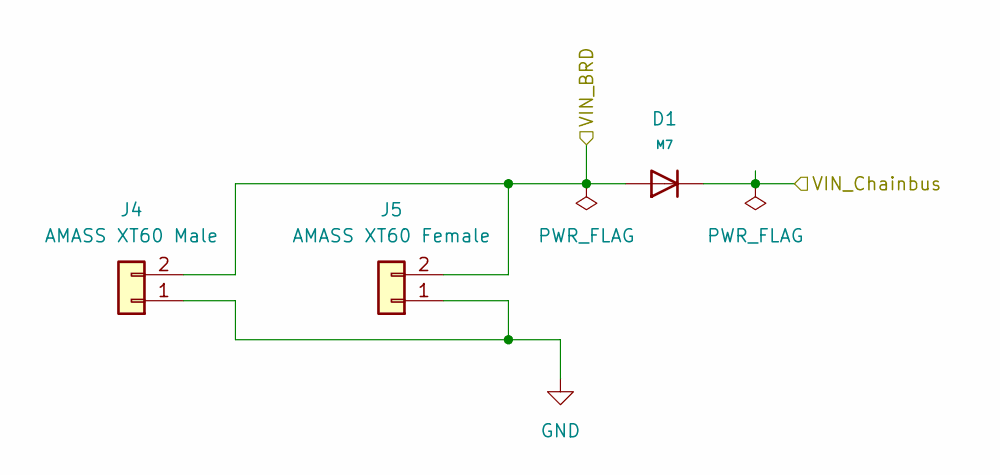
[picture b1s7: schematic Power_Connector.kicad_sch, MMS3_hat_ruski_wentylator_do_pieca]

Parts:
D1: M7; D_SMA; Forward Voltage (Vf@If) 1.1V@1A; Reverse Voltage (Vr) 1kV; Part M7; LCSC C95872
J4: AMASS XT60 Male; AMASS_XT60PW-M_1x02_P7.20mm_Horizontal; LCSC C98732
J5: AMASS XT60 Female; AMASS_XT60PW-F_1x02_P7.20mm_Horizontal; LCSC C428722

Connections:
/Boost Converter/Boost_In: D1.2, J4.2, J5.2; also elsewhere on the board
BRD_VIN: D1.1; also elsewhere on the board
GND: J4.1, J5.1; also elsewhere on the board

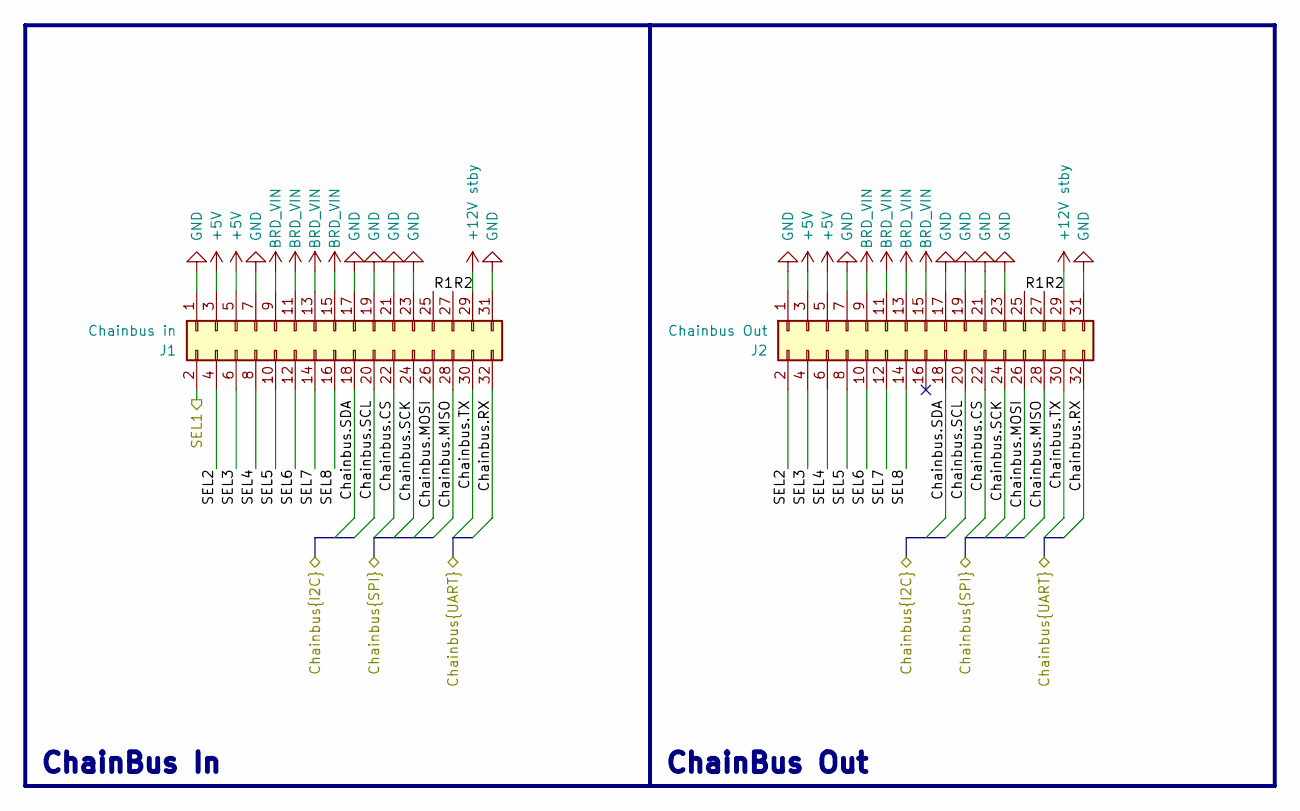
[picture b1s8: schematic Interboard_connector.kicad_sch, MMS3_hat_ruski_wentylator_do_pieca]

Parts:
J1: Chainbus in; PinHeader_2x16_P2.54mm_Vertical_SMD
J2: Chainbus Out; PinSocket_2x16_P2.54mm_Vertical_SMD

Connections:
+5V: J1.3, J1.5, J2.3, J2.5; also elsewhere on the board
+12V stby: J1.29, J2.29
/Bus_switch/Chainbus_In.SCL: J1.20, J2.20; also elsewhere on the board
/Bus_switch/Chainbus_In.SDA: J1.18, J2.18; also elsewhere on the board
/Bus_switch/SEL1: J1.2; also elsewhere on the board
/Interboard_connector/Chainbus.CS: J1.22, J2.22
/Interboard_connector/Chainbus.MISO: J1.28, J2.28
/Interboard_connector/Chainbus.MOSI: J1.26, J2.26
/Interboard_connector/Chainbus.RX: J1.32, J2.32
/Interboard_connector/Chainbus.SCK: J1.24, J2.24
/Interboard_connector/Chainbus.TX: J1.30, J2.30
/Interboard_connector/R1: J1.25, J2.25
/Interboard_connector/R2: J1.27, J2.27
/Interboard_connector/SEL2: J1.4, J2.2
/Interboard_connector/SEL3: J1.6, J2.4
/Interboard_connector/SEL4: J1.8, J2.6
/Interboard_connector/SEL5: J1.10, J2.8
/Interboard_connector/SEL6: J1.12, J2.10
/Interboard_connector/SEL7: J1.14, J2.12
/Interboard_connector/SEL8: J1.16, J2.14
BRD_VIN: J1.9, J1.11, J1.13, J1.15, J2.9, J2.11, J2.13, J2.15; also elsewhere on the board
GND: J1.1, J1.7, J1.17, J1.19, J1.21, J1.23, J1.31, J2.1, J2.7, J2.17, J2.19, J2.21, J2.23, J2.31; also elsewhere on the board

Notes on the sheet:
ChainBus In
ChainBus Out
